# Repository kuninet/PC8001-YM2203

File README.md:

# PC-8001用 YM2203 FM音源ボード

## 概要
- PC-8001用 YM2203 FM音源ボードです。
- PC-8001 外部CPUバスに接続できます。
- 出力端子(イヤホンジャック)からアンプ経由に接続してください。

## 注意
- 試作確認しているところなので、間違いがあったらご指摘ください。

## ライセンス
- MITライセンスで公開します。

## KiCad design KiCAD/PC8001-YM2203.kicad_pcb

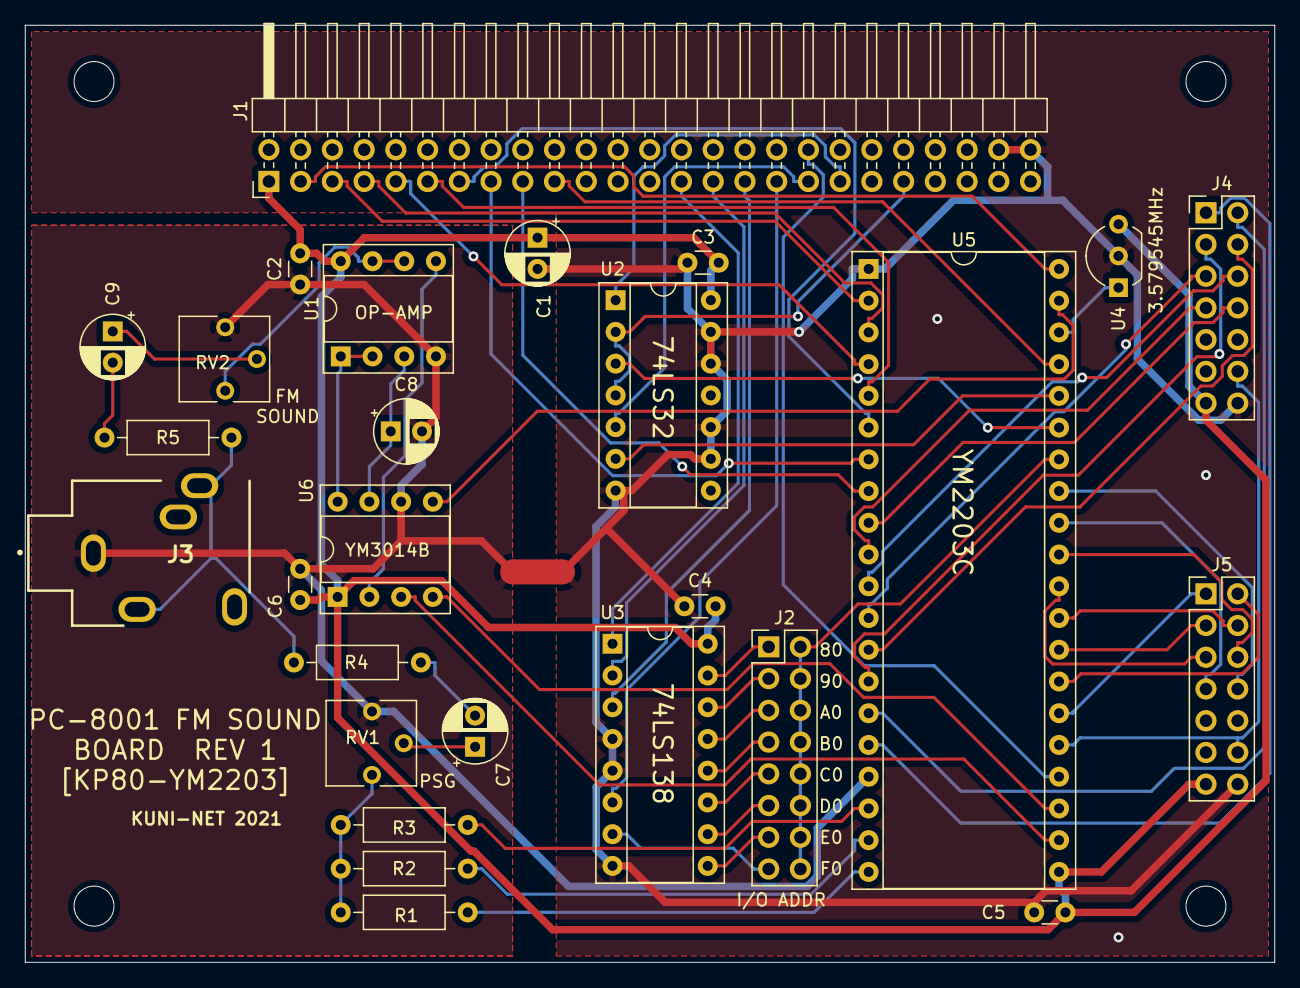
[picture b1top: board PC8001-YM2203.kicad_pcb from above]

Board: 2 copper layers, 100.0 x 75.0 mm, 32 parts (0 on the bottom side), 65 nets.

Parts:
C1, C7, C8, C9: 10u; CP_Radial_D5.0mm_P2.50mm
C2, C3, C4, C5, C6: 0.1u; C_Disc_D3.0mm_W1.6mm_P2.50mm
H1, H2, H3, H4: MountingHole; MountingHole_3.2mm_M3
J1: PC-8001 ext BUS; PinHeader_2x25_P2.54mm_Horizontal
J2: ADDR JP; PinHeader_2x08_P2.54mm_Vertical
J3: Audio-Jack-3_2Switches; AJ-1780
J4: A-CON; PinHeader_2x07_P2.54mm_Vertical
J5: B-CON; PinHeader_2x07_P2.54mm_Vertical
NT1: Net-Tie_2; NetTie-2_SMD_Pad2.0mm
R1, R2, R3, R4, R5: 1k; R_Axial_DIN0207_L6.3mm_D2.5mm_P10.16mm_Horizontal
RV1: 1k; Potentiometer_Vishay_T73YP_Vertical
RV2: 10k; Potentiometer_Vishay_T73YP_Vertical
U1: NJM5532DD; DIP-8_W7.62mm_Socket
U2: 74LS32; DIP-14_W7.62mm_Socket
U3: 74LS138; DIP-16_W7.62mm_Socket
U4: DLO555MB; TO-92_Inline_Wide
U5: YM2203; DIP-40_W15.24mm_Socket
U6: YM3014B; DIP-8_W7.62mm_Socket

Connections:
/$80: J2.1, U3.15
/$90: J2.3, U3.14
/$A0: J2.5, U3.13
/$B0: J2.7, U3.12
/$C0: J2.9, U3.11
/$D0: J2.11, U3.10
/$E0: J2.13, U3.9
/$F0: J2.15, U3.7
/A0: J1.19, U5.37
/A4: J1.27, U3.1
/A5: J1.29, U3.2
/A6: J1.31, U3.3
/A7: J1.33, U3.6
/D0: J1.3, U5.40
/D1: J1.5, U5.2
/D2: J1.7, U5.3
/D3: J1.9, U5.4
/D4: J1.11, U5.5
/D5: J1.13, U5.6
/D6: J1.15, U5.7
/D7: J1.17, U5.8
/IOA0: J4.1, U5.16
/IOA1: J4.2, U5.15
/IOA2: J4.3, U5.14
/IOA3: J4.4, U5.13
/IOA4: J4.5, U5.12
/IOA5: J4.6, U5.11
/IOA6: J4.7, U5.10
/IOA7: J4.8, U5.9
/IOB0: J5.1, U5.26
/IOB1: J5.2, U5.27
/IOB2: J5.3, U5.28
/IOB3: J5.4, U5.29
/IOB4: J5.5, U5.30
/IOB5: J5.6, U5.31
/IOB6: J5.7, U5.32
/IOB7: J5.8, U5.33
/~IORD: U2.6, U5.36
/~IOREQ: J1.41, U2.2, U2.4
/~IOWR: U2.3, U5.35
/~IRQ: J4.12, J5.12, U5.25
/~RD: J1.35, U2.5
/~RESET: J1.36, U5.24
/~WR: J1.37, U2.1
GND: C1.2, C3.1, C4.1, C5.1, J1.48, J1.50, J4.14, J5.14, NT1.2, U2.7, U2.9, U2.10, U2.12, U2.13, U3.4, U3.5, U3.8, U4.2, U5.1
GNDA: C2.1, C6.1, C8.2, J3.1, NT1.1, RV1.3, RV2.3, U1.4, U5.17, U6.6
unnamed: C7.1, RV1.2
unnamed: C7.2, R4.2
unnamed: C8.1, U1.3, U6.7
unnamed: C9.1, RV2.2
unnamed: C9.2, R5.2
unnamed: J2.2, J2.4, J2.6, J2.8, J2.10, J2.12, J2.14, J2.16, U5.34
unnamed: J3.2, J3.5, R4.1, R5.1
unnamed: R1.1, R2.1, R3.1, RV1.1
unnamed: R1.2, U5.20
unnamed: R2.2, U5.19
unnamed: R3.2, U5.18
unnamed: RV2.1, U1.6, U1.7
unnamed: U1.1, U1.2, U6.8
unnamed: U1.5, U6.2
unnamed: U4.1, U5.38
unnamed: U5.22, U6.3
unnamed: U5.23, U6.4
unnamed: U5.39, U6.5
VCC: C1.1, C2.2, C3.2, C4.2, C5.2, C6.2, J1.1, J4.13, J5.13, U1.8, U2.14, U3.16, U4.3, U5.21, U6.1

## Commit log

2020-12-06 init commit
2020-12-06 回路図イメージ追加
2020-12-06 74HC32、HC138は74LS32、LS138の間違いだったので修正
2020-12-06 回路図74LS版へ差し替え
2020-12-06 演奏サンプル 作成開始
2020-12-06 PC-8001用VGMプレーヤー ベータ版
2021-02-15 I/O端子設置、プリントパターン検討
2021-02-18 ガーバーデータ出力
2021-03-15 シルク見直し・ガーバー再出力
2021-03-15 シルク再見直し・ガーバー再出力
2021-03-20 回路図差し替え
